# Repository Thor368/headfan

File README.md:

# headfan
board to controll a headfan from a single liion cell

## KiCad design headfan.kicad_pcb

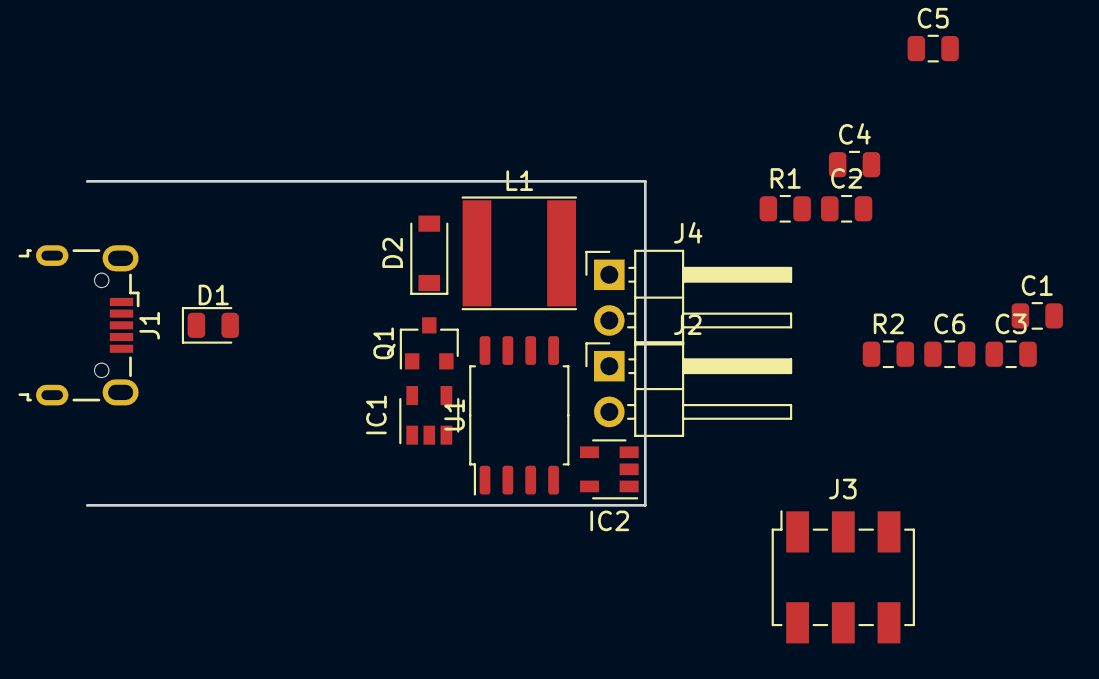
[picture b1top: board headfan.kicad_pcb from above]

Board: 2 copper layers, 31.0 x 18.0 mm, 19 parts (0 on the bottom side), 12 nets, no tracks yet.

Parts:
C1, C2: 1u/6V3; C_0805_2012Metric
C3: 100n; C_0805_2012Metric
C4: 10u/6V3; C_0805_2012Metric
C5: 10n; C_0805_2012Metric
C6: 10u/25V; C_0805_2012Metric
D1: green; LED_0805_2012Metric
D2: DIODE; D_SOD-123
IC1: MCP73811; SOT-23-5
IC2: SI7217; SOT-23-5
J1: USB; USB_Micro-B_Wuerth_629105150521
J2: Battery; PinHeader_1x02_P2.54mm_Horizontal
J3: AVR-ISP-6; Samtec_HLE-103-02-xxx-DV_2x03_P2.54mm_Horizontal
J4: Fan; PinHeader_1x02_P2.54mm_Horizontal
L1: NRS6028T101MMGJ; L_Taiyo-Yuden_NR-60xx
Q1: Q_NMOS_GSD; SOT-23
R1: 100R; R_0805_2012Metric
R2: 10k; R_0805_2012Metric
U1: ATtiny13-20SSU; SOIC-8_5.23x5.23mm_P1.27mm

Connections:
+BATT: C2.2, C3.1, C4.2, D2.1, IC1.3, IC2.4, J2.1, J3.2, U1.3, U1.8
GND: C1.1, C2.1, C3.2, C4.1, C5.1, C6.2, D1.1, IC1.2, IC2.2, J1.5, J1.6, J2.2, J3.6, J4.2, Q1.2, R2.1, U1.4
unnamed: C1.2, IC1.1, IC1.4, IC1.5, J1.1
unnamed: C5.2, J3.5, U1.1
unnamed: C6.1, J4.1, L1.2
unnamed: D1.2, R1.2
unnamed: D2.2, L1.1, Q1.3
unnamed: IC2.3, J3.3, U1.7
unnamed: IC2.5, U1.2
unnamed: J1.2, J1.3
unnamed: J3.1, R1.1, U1.6
unnamed: J3.4, Q1.1, R2.2, U1.5

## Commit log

2019-09-02 - µC, hall, step-up wired - battery, charger missing
2019-09-25 - added charge controller - started layout
